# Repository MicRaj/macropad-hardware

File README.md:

# macropad-hardware
KiCAD PCB design files for the macropad.

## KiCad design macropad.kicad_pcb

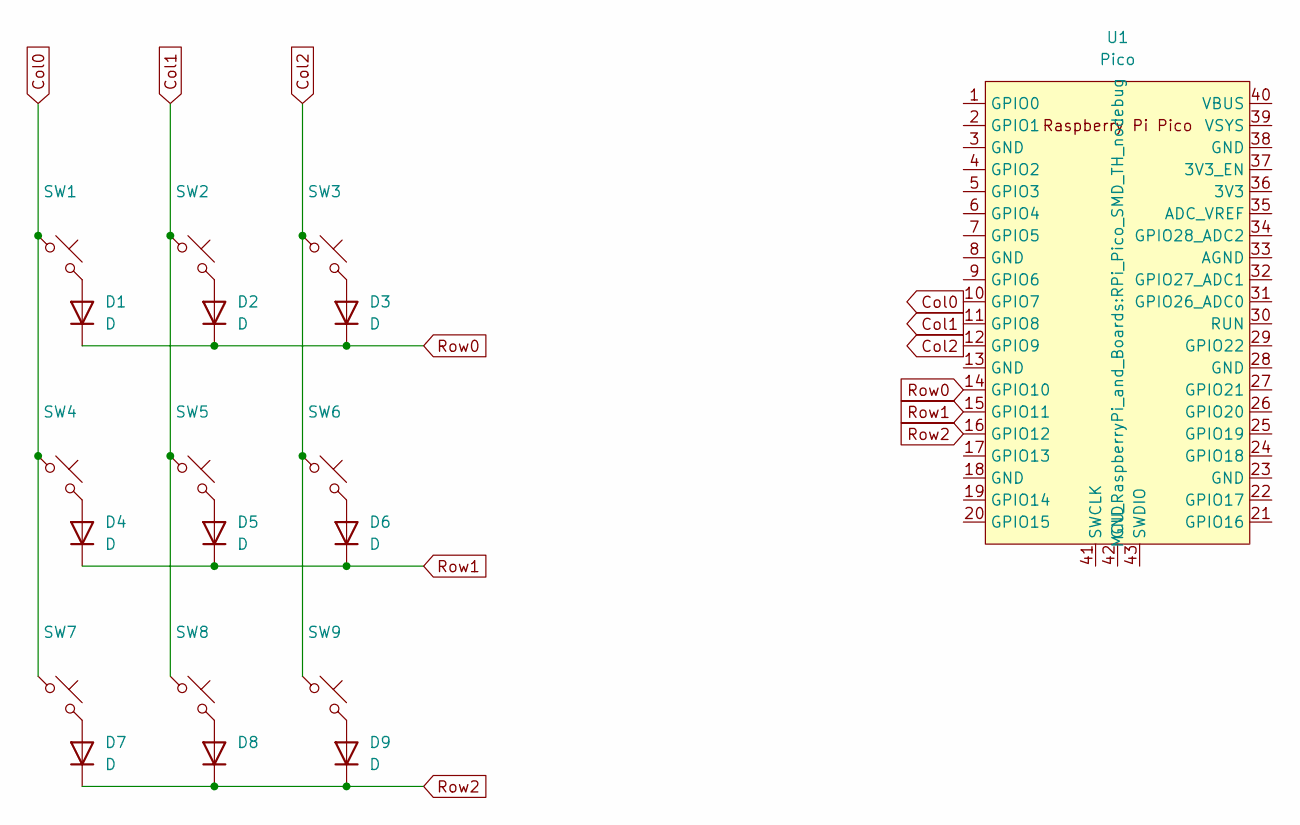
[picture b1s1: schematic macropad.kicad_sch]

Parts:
D1, D2, D3, D4, D5, D6, D7, D8, D9: D; D_DO-35_SOD27_P7.62mm_Horizontal
SW1, SW2, SW3, SW4, SW5, SW6, SW7, SW8, SW9: SW_Push_45deg; SW_Cherry_MX_1.00u_Plate
U1: Pico; RPi_Pico_SMD_TH_nodebug

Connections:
Col0: SW1.1, SW4.1, SW7.1, U1.10 (GPIO7)
Col1: SW2.1, SW5.1, SW8.1, U1.11 (GPIO8)
Col2: SW3.1, SW6.1, SW9.1, U1.12 (GPIO9)
unnamed: D1.2 (A), SW1.2
unnamed: D2.2 (A), SW2.2
unnamed: D3.2 (A), SW3.2
unnamed: D4.2 (A), SW4.2
unnamed: D5.2 (A), SW5.2
unnamed: D6.2 (A), SW6.2
unnamed: D7.2 (A), SW7.2
unnamed: D8.2 (A), SW8.2
unnamed: D9.2 (A), SW9.2
Row0: D1.1 (K), D2.1 (K), D3.1 (K), U1.14 (GPIO10)
Row1: D4.1 (K), D5.1 (K), D6.1 (K), U1.15 (GPIO11)
Row2: D7.1 (K), D8.1 (K), D9.1 (K), U1.16 (GPIO12)

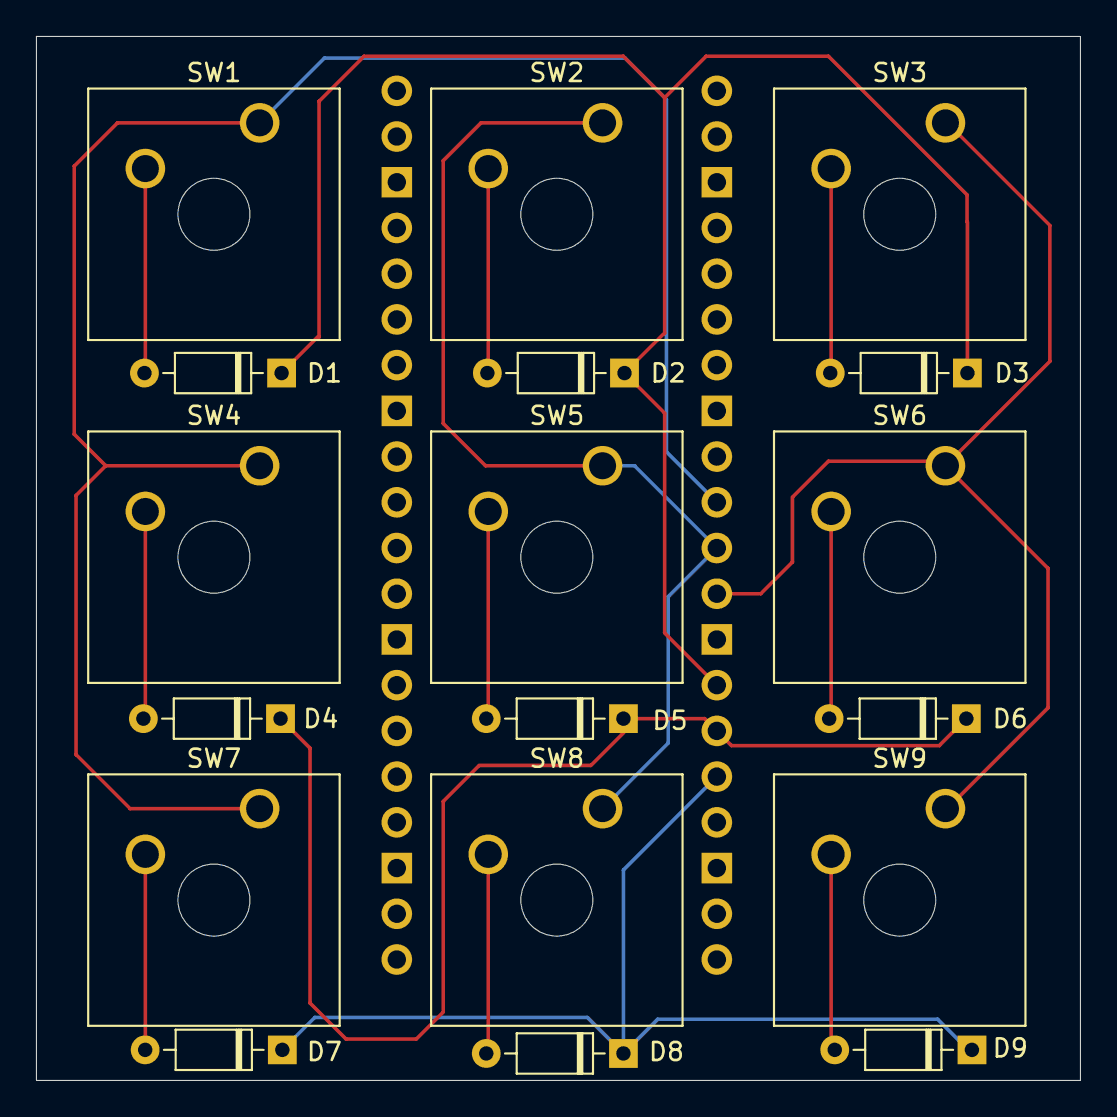
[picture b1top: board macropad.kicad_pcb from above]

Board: 2 copper layers, 58.0 x 58.0 mm, 19 parts (1 on the bottom side), 15 nets.

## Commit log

2025-03-17 Added pcb design files
